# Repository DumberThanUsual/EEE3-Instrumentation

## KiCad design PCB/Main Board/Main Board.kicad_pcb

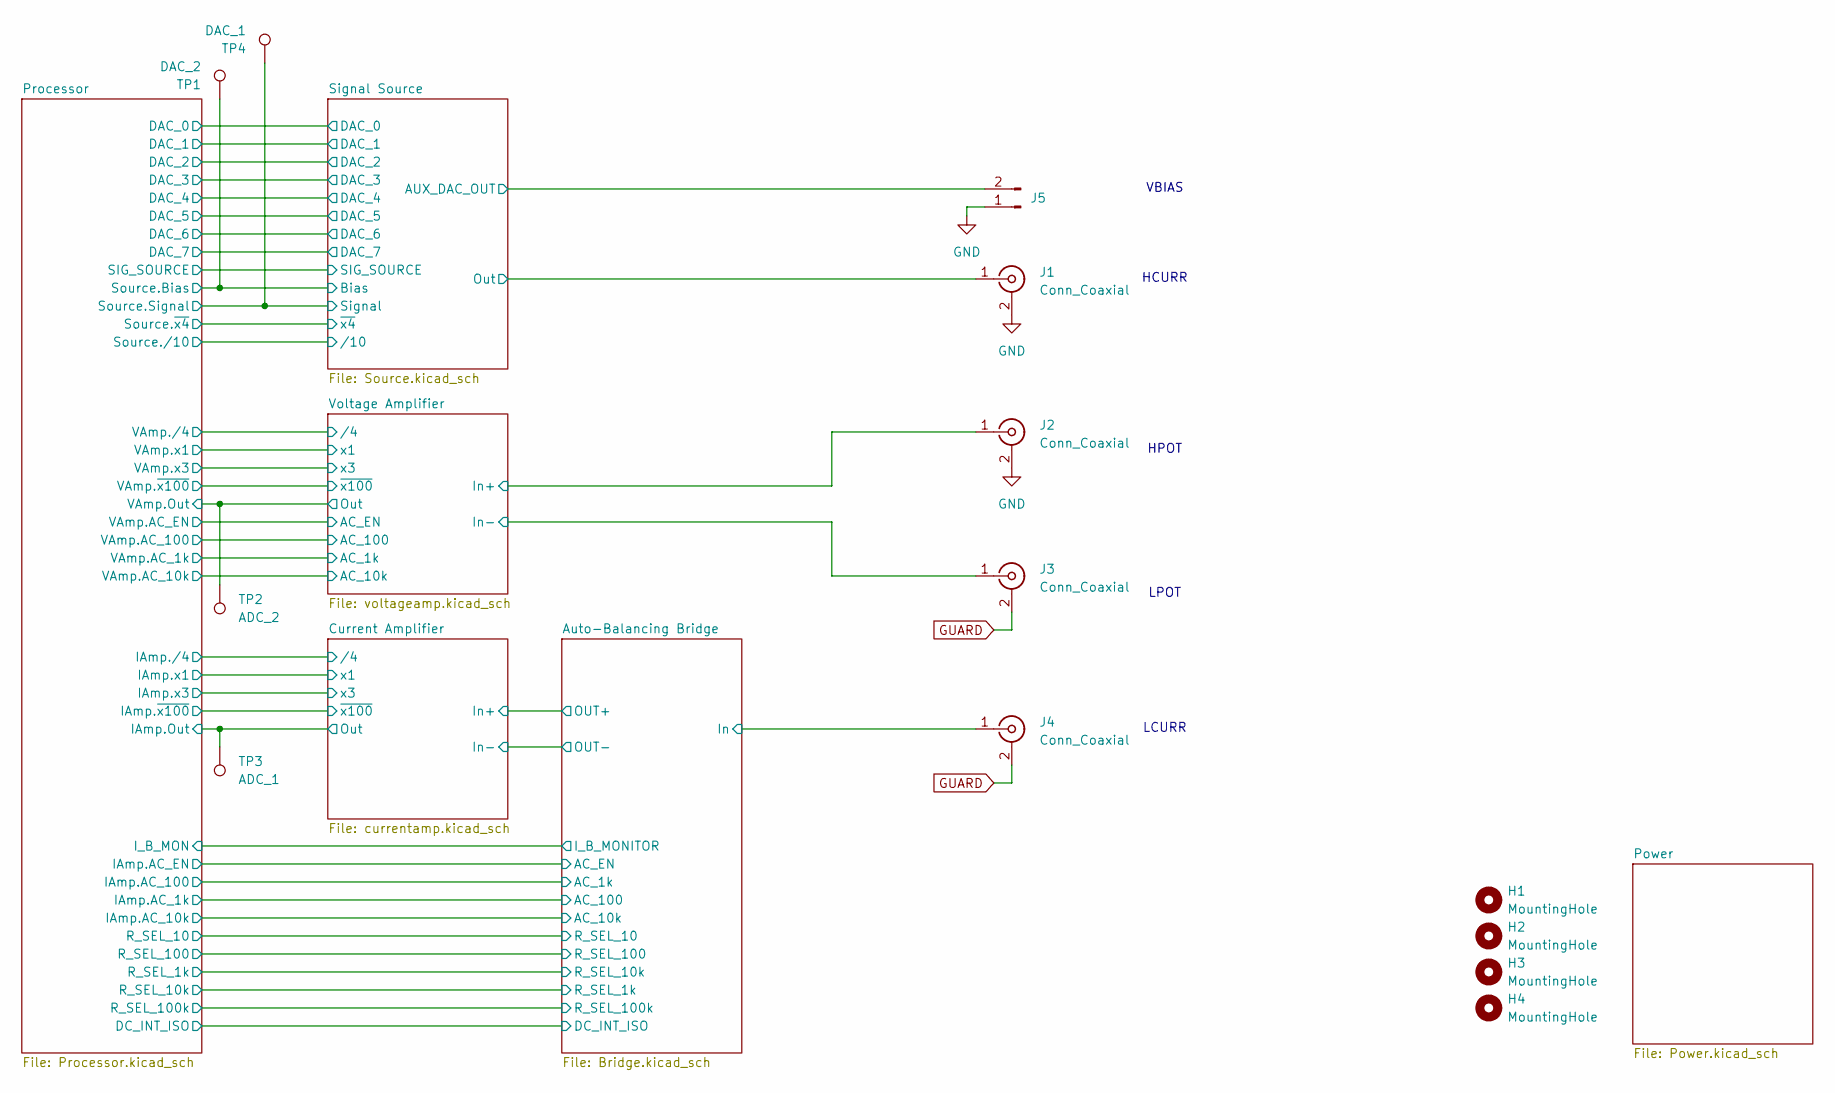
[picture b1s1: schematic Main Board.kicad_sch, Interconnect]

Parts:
H1, H2, H3, H4: MountingHole; MountingHole_3.2mm_M3
J1, J2, J3, J4: Conn_Coaxial; BNC_Amphenol_B6252HB-NPP3G-50_Horizontal
J5: Conn_01x02_Pin; PinHeader_1x02_P2.54mm_Vertical
TP1: DAC_2; TestPoint_Pad_2.0x2.0mm
TP2: ADC_2; TestPoint_Pad_2.0x2.0mm
TP3: ADC_1; TestPoint_Pad_2.0x2.0mm
TP4: DAC_1; TestPoint_Pad_2.0x2.0mm

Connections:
/Auto-Balancing Bridge/In: J4.1 (In); also elsewhere on the board
/Current Amplifier/Out: TP3.1; also elsewhere on the board
/Processor/Source.Bias: TP1.1; also elsewhere on the board
/Processor/Source.Signal: TP4.1; also elsewhere on the board
/Processor/VAmp.Out: TP2.1; also elsewhere on the board
/Signal Source/AUX_DAC_OUT: J5.2; also elsewhere on the board
/Signal Source/Out: J1.1 (In); also elsewhere on the board
/Voltage Amplifier/In+: J2.1 (In); also elsewhere on the board
/Voltage Amplifier/In-: J3.1 (In); also elsewhere on the board
GND: J1.2 (Ext), J2.2 (Ext), J5.1; also elsewhere on the board
GUARD: J3.2 (Ext), J4.2 (Ext); also elsewhere on the board

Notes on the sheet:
LPOT
HCURR
VBIAS
LCURR
HPOT

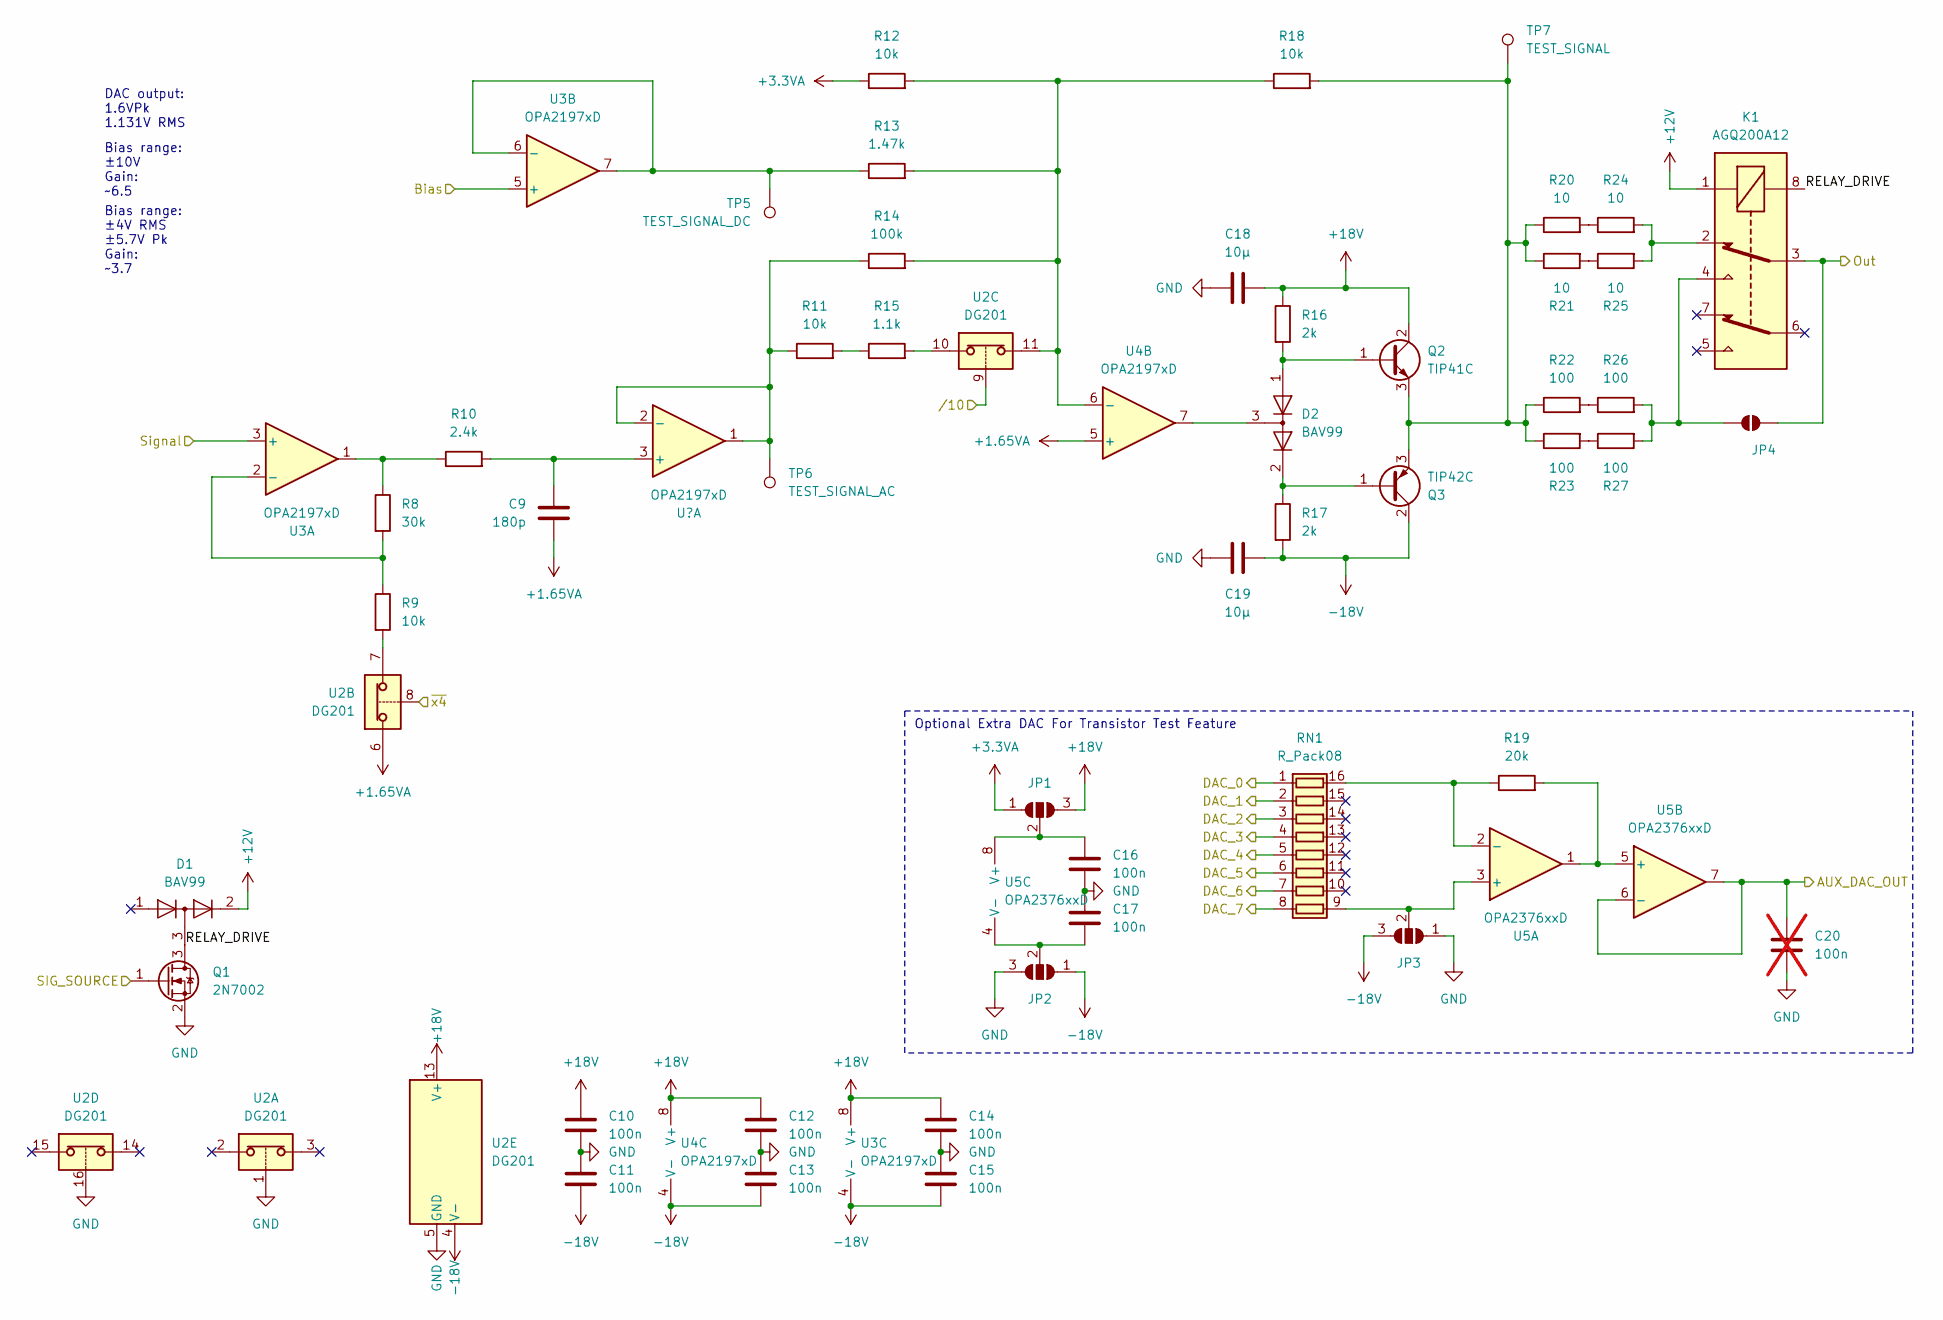
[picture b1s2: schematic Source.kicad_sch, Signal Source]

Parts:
C9: 180p; C_0805_2012Metric
C10, C11, C12, C13, C14, C15, C16, C17: 100n; C_0805_2012Metric
C18, C19: 10µ; C_0805_2012Metric
C20: 100n; C_0805_2012Metric; not fitted
D1, D2: BAV99; SOT-23
JP1, JP2, JP3: SolderJumper_3_Open; SolderJumper-3_P1.3mm_Open_RoundedPad1.0x1.5mm
JP4: SolderJumper_2_Open; SolderJumper-2_P1.3mm_Open_RoundedPad1.0x1.5mm
K1: AGQ200A12; RELAY_AGQ_A_PAN; Mouser Part Number 769-AGQ200A12
Q1: 2N7002; SOT-23
Q2: TIP41C; TO-220-3_Vertical
Q3: TIP42C; TO-220-3_Vertical
R8: 30k; R_0805_2012Metric
R9, R11, R12, R18: 10k; R_0805_2012Metric
R10: 2.4k; R_0805_2012Metric
R13: 1.47k; R_0805_2012Metric
R14: 100k; R_0805_2012Metric
R15: 1.1k; R_0805_2012Metric
R16, R17: 2k; R_0805_2012Metric
R19: 20k; R_0805_2012Metric
R20, R21, R24, R25: 10; R_2512_6332Metric
R22, R23, R26, R27: 100; R_0805_2012Metric
RN1: R_Pack08; SOIC-16_3.9x9.9mm_P1.27mm
TP5: TEST_SIGNAL_DC; TestPoint_Pad_2.0x2.0mm
TP6: TEST_SIGNAL_AC; TestPoint_Pad_2.0x2.0mm
TP7: TEST_SIGNAL; TestPoint_Pad_2.0x2.0mm
U2: DG201; SOIC-16_3.9x9.9mm_P1.27mm
U3, U4: OPA2197xD; SOIC-8_3.9x4.9mm_P1.27mm
U5: OPA2376xxD; SOIC-8_3.9x4.9mm_P1.27mm

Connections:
+1.65VA: C9.2, U2.6, U4.3 (+), U4.5 (+); also elsewhere on the board
+3.3VA: JP1.1 (A), R12.1; also elsewhere on the board
+12V: D1.2 (A), K1.1; also elsewhere on the board
+18V: C10.1, C12.1, C14.1, C18.2, JP1.3 (B), Q2.2 (C), R16.1, U2.13 (V+), U3.8 (V+), U4.8 (V+); also elsewhere on the board
-18V: C11.2, C13.2, C15.2, C19.2, JP2.1 (A), JP3.3 (B), Q3.2 (C), R17.2, U2.4 (V-), U3.4 (V-), U4.4 (V-); also elsewhere on the board
/Processor/DAC_0: RN1.1 (R1.1); also elsewhere on the board
/Processor/DAC_1: RN1.2 (R2.1); also elsewhere on the board
/Processor/DAC_2: RN1.3 (R3.1); also elsewhere on the board
/Processor/DAC_3: RN1.4 (R4.1); also elsewhere on the board
/Processor/DAC_4: RN1.5 (R5.1); also elsewhere on the board
/Processor/DAC_5: RN1.6 (R6.1); also elsewhere on the board
/Processor/DAC_6: RN1.7 (R7.1); also elsewhere on the board
/Processor/DAC_7: RN1.8 (R8.1); also elsewhere on the board
/Processor/SIG_SOURCE: Q1.1 (G); also elsewhere on the board
/Processor/Source.Bias: U3.5 (+); also elsewhere on the board
/Processor/Source.Signal: U3.3 (+); also elsewhere on the board
/Processor/Source./10: U2.9; also elsewhere on the board
/Processor/Source.~x4: U2.8; also elsewhere on the board
/Signal Source/AUX_DAC_OUT: C20.1, U5.6 (-), U5.7; also elsewhere on the board
/Signal Source/Out: JP4.1 (A), K1.3; also elsewhere on the board
/Signal Source/RELAY_DRIVE: D1.3 (K), K1.8, Q1.3 (D)
GND: C10.2, C11.1, C12.2, C13.1, C14.2, C15.1, C16.2, C17.1, C18.1, C19.1, C20.2, JP2.3 (B), JP3.1 (A), Q1.2 (S), U2.1, U2.5 (GND), U2.16; also elsewhere on the board
unnamed: D2.2 (A), Q3.1 (B), R17.1
unnamed: D2.3 (K), U4.7
unnamed: C16.1, JP1.2 (C), U5.8 (V+)
unnamed: C17.2, JP2.2 (C), U5.4 (V-)
unnamed: JP3.2 (C), RN1.9 (R8.2), U5.3 (+)
unnamed: JP4.2 (B), K1.4, R26.2, R27.2
unnamed: K1.2, R24.2, R25.2
unnamed: D2.1 (K), Q2.1 (B), R16.2
unnamed: Q2.3 (E), Q3.3 (E), R18.2, R20.1, R21.1, R22.1, R23.1, TP7.1
unnamed: R9.2, U2.7
unnamed: R8.1, R10.1, U3.1
unnamed: R11.1, R14.1, TP6.1, U4.1
unnamed: R11.2, R15.1
unnamed: R15.2, U2.10
unnamed: R20.2, R24.1
unnamed: R21.2, R25.1
unnamed: R22.2, R26.1
unnamed: R23.2, R27.1
unnamed: R19.1, RN1.16 (R1.2), U5.2 (-)
unnamed: R8.2, R9.1, U3.2 (-)
unnamed: R13.1, TP5.1, U3.6 (-), U3.7
unnamed: C9.1, R10.2, U4.2 (-)
unnamed: R12.2, R13.2, R14.2, R18.1, U2.11, U4.6 (-)
unnamed: R19.2, U5.1, U5.5 (+)

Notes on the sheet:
Optional Extra DAC For Transistor Test Feature
Bias range: ±10V Gain: ~6.5
DAC output: 1.6VPk 1.131V RMS
Bias range: ±4V RMS ±5.7V Pk Gain: ~3.7

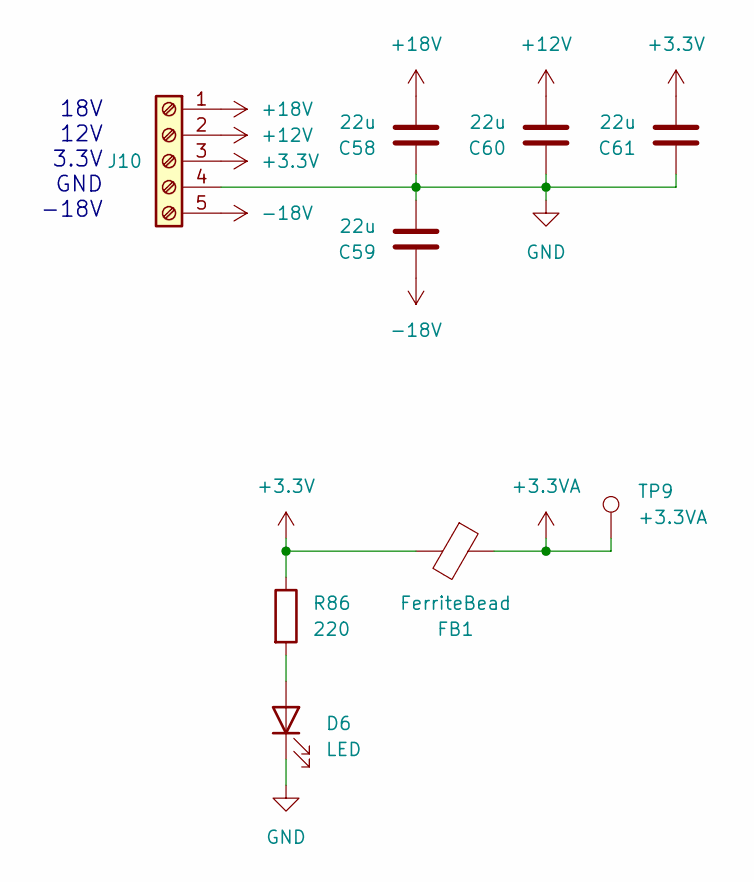
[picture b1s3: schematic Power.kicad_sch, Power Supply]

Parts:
C58, C59, C60, C61: 22u; C_1210_3225Metric
D6: LED; LED_0805_2012Metric
FB1: FerriteBead; L_0805_2012Metric
J10: Screw_Terminal_01x05; TerminalBlock_Phoenix_MKDS-1,5-5_1x05_P5.00mm_Horizontal
R86: 220; R_0805_2012Metric
TP9: +3.3VA; TestPoint_Pad_2.0x2.0mm

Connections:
+3.3V: C61.2, FB1.2, J10.3, R86.1; also elsewhere on the board
+3.3VA: FB1.1, TP9.1; also elsewhere on the board
+12V: C60.2, J10.2; also elsewhere on the board
+18V: C58.2, J10.1; also elsewhere on the board
-18V: C59.1, J10.5; also elsewhere on the board
GND: C58.1, C59.2, C60.1, C61.1, D6.1 (K), J10.4; also elsewhere on the board
unnamed: D6.2 (A), R86.2

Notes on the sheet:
18V 12V 3.3V GND -18V

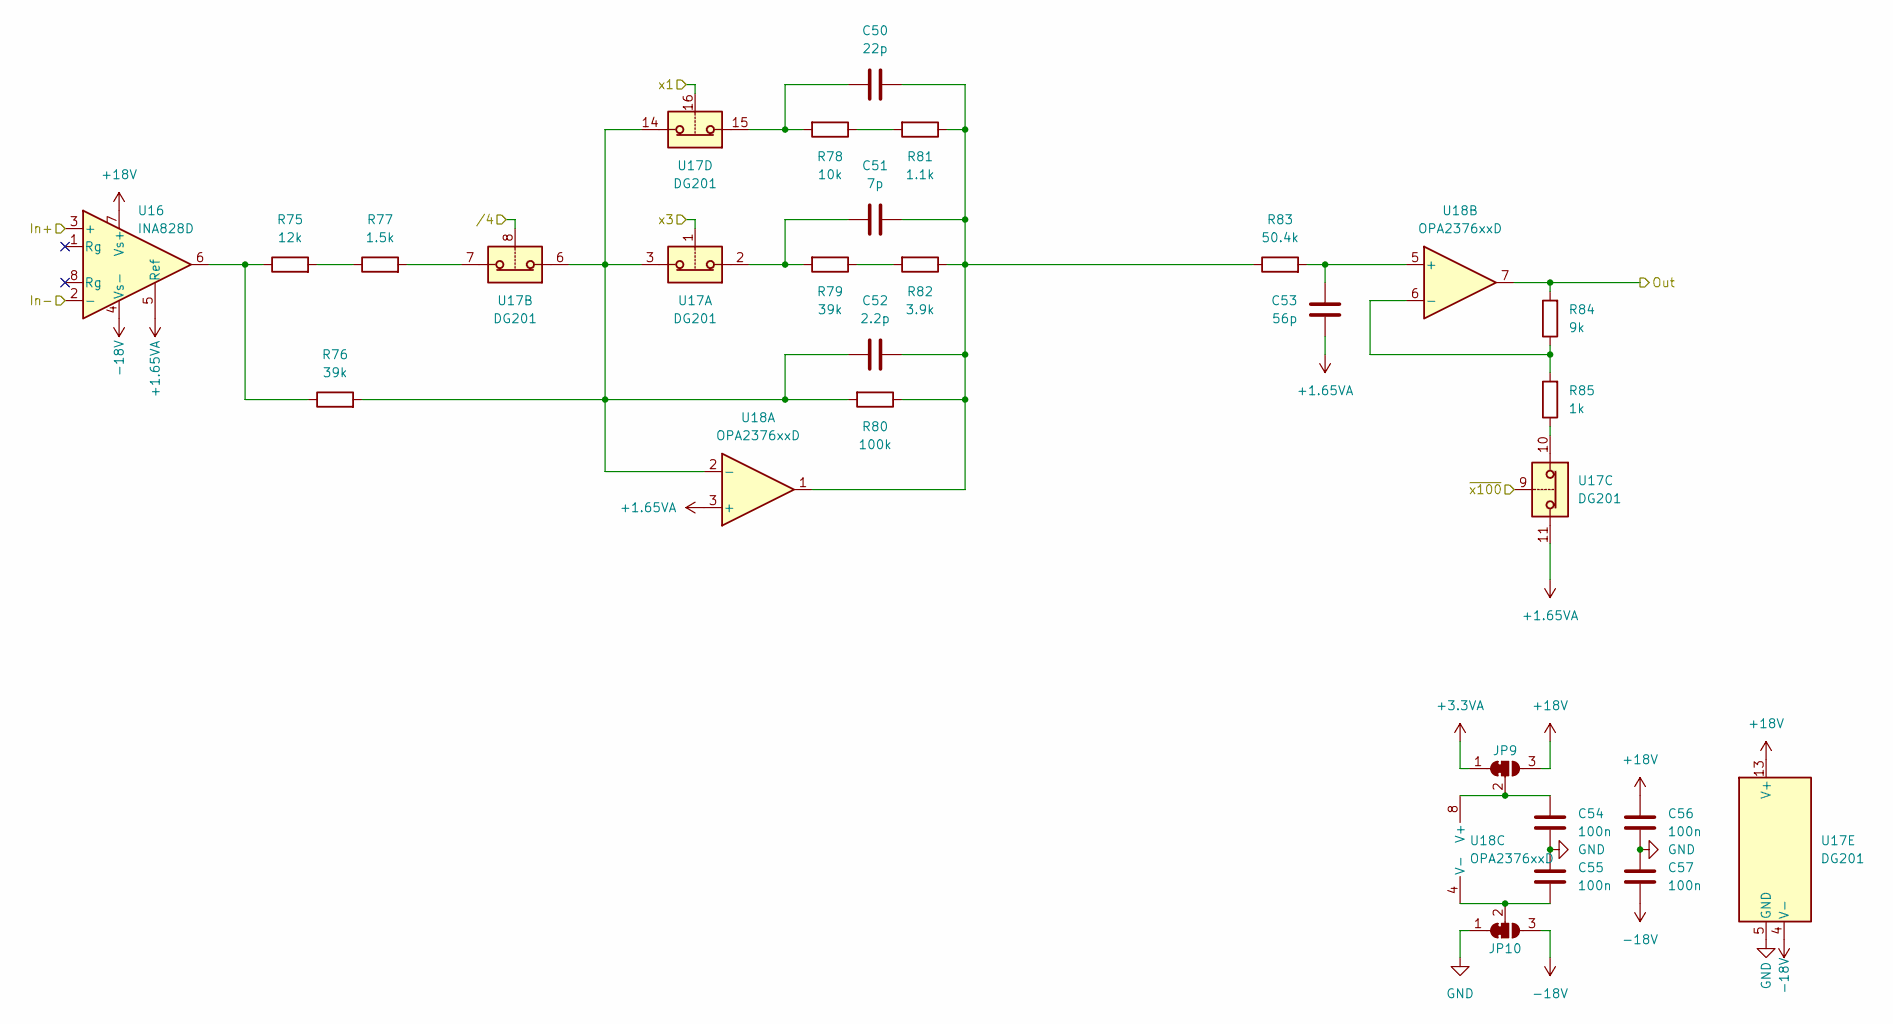
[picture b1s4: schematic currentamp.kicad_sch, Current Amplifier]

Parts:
C50: 22p; C_0805_2012Metric
C51: 7p; C_0805_2012Metric
C52: 2.2p; C_0805_2012Metric
C53: 56p; C_0805_2012Metric
C54, C55, C56, C57: 100n; C_0805_2012Metric
JP9, JP10: SolderJumper_3_Bridged12; SolderJumper-3_P1.3mm_Bridged12_RoundedPad1.0x1.5mm
R75: 12k; R_0805_2012Metric
R76, R79: 39k; R_0805_2012Metric
R77: 1.5k; R_0805_2012Metric
R78: 10k; R_0805_2012Metric
R80: 100k; R_0805_2012Metric
R81: 1.1k; R_0805_2012Metric
R82: 3.9k; R_0805_2012Metric
R83: 50.4k; R_0805_2012Metric
R84: 9k; R_0805_2012Metric
R85: 1k; R_0805_2012Metric
U16: INA828D; SOIC-8_3.9x4.9mm_P1.27mm
U17: DG201; SOIC-16_3.9x9.9mm_P1.27mm
U18: OPA2376xxD; SOIC-8_3.9x4.9mm_P1.27mm

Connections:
+1.65VA: C53.2, U16.5 (Ref), U17.11, U18.3 (+); also elsewhere on the board
+3.3VA: JP9.1 (A); also elsewhere on the board
+18V: C56.1, JP9.3 (B), U16.7 (Vs+), U17.13 (V+); also elsewhere on the board
-18V: C57.2, JP10.3 (B), U16.4 (Vs-), U17.4 (V-); also elsewhere on the board
/Auto-Balancing Bridge/In: U16.3 (+); also elsewhere on the board
/Auto-Balancing Bridge/OUT+: U16.2 (-); also elsewhere on the board
/Current Amplifier/Out: R84.2, U18.7; also elsewhere on the board
/Current Amplifier/x1: U17.16; also elsewhere on the board
/Current Amplifier/x3: U17.1; also elsewhere on the board
/Current Amplifier//4: U17.8; also elsewhere on the board
/Current Amplifier/~x100: U17.9; also elsewhere on the board
GND: C54.2, C55.1, C56.2, C57.1, JP10.1 (A), U17.5 (GND); also elsewhere on the board
unnamed: C50.1, R78.2, U17.15
unnamed: C50.2, C51.2, C52.2, R80.1, R81.1, R82.1, R83.1, U18.1
unnamed: C51.1, R79.2, U17.2
unnamed: C54.1, JP9.2 (C), U18.8 (V+)
unnamed: C55.2, JP10.2 (C), U18.4 (V-)
unnamed: R75.1, R76.1, U16.6
unnamed: R75.2, R77.1
unnamed: R77.2, U17.7
unnamed: R78.1, R81.2
unnamed: R79.1, R82.2
unnamed: R85.1, U17.10
unnamed: C52.1, R76.2, R80.2, U17.3, U17.6, U17.14, U18.2 (-)
unnamed: C53.1, R83.2, U18.5 (+)
unnamed: R84.1, R85.2, U18.6 (-)

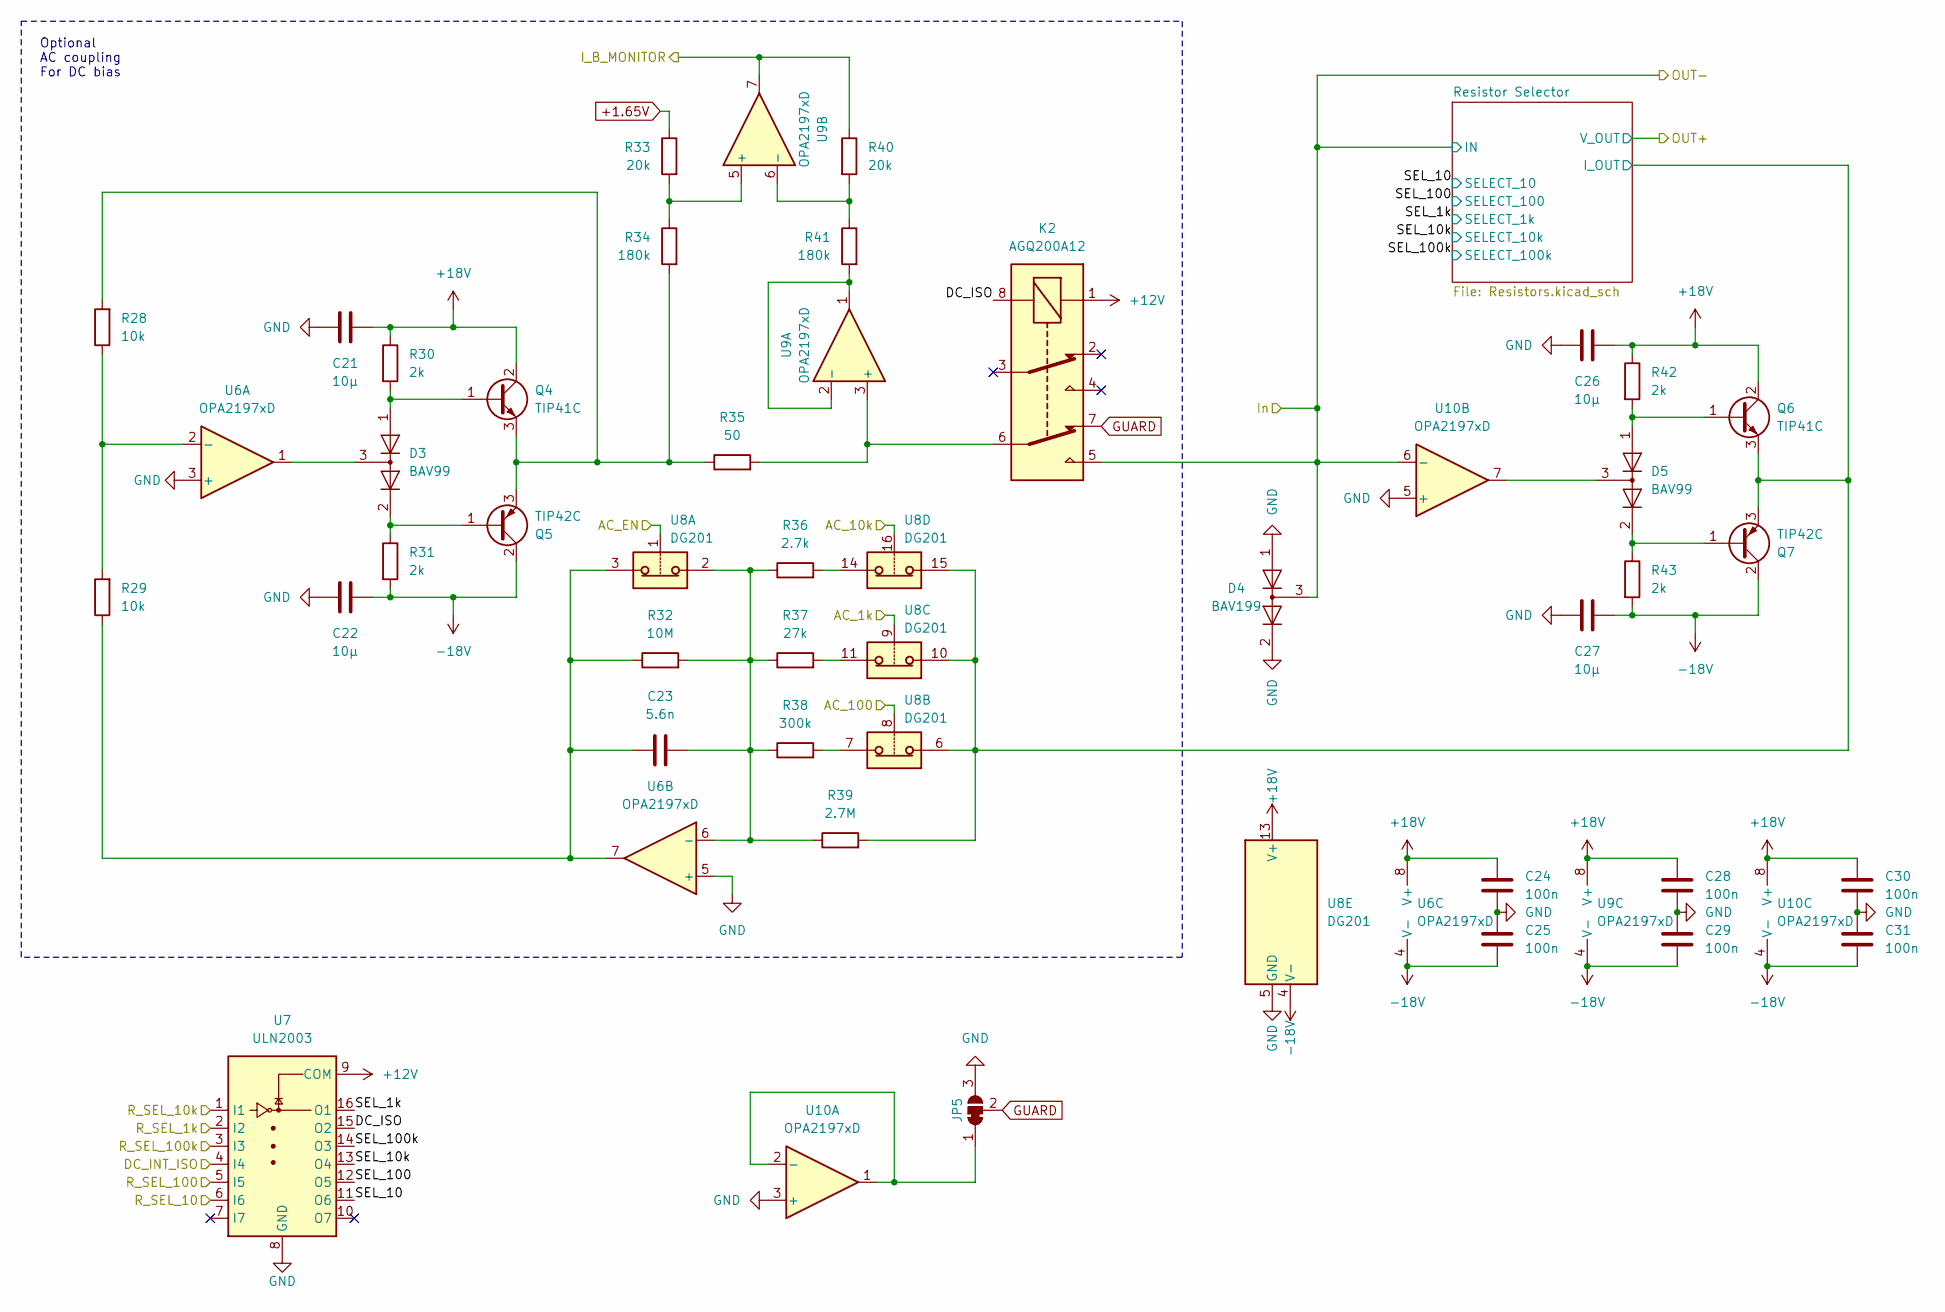
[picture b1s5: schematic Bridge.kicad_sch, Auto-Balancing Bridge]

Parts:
C21, C22, C26, C27: 10µ; C_0805_2012Metric
C23: 5.6n; C_0805_2012Metric
C24, C25, C28, C29, C30, C31: 100n; C_0805_2012Metric
D3, D5: BAV99; SOT-23
D4: BAV199; SOT-23
JP5: SolderJumper_3_Bridged12; SolderJumper-3_P1.3mm_Bridged12_RoundedPad1.0x1.5mm
K2: AGQ200A12; RELAY_AGQ_A_PAN; Mouser Part Number 769-AGQ200A12
Q4, Q6: TIP41C; TO-220-3_Vertical
Q5, Q7: TIP42C; TO-220-3_Vertical
R28, R29: 10k; R_0805_2012Metric
R30, R31, R42, R43: 2k; R_0805_2012Metric
R32: 10M; R_0805_2012Metric
R33, R40: 20k; R_0805_2012Metric
R34, R41: 180k; R_0805_2012Metric
R35: 50; R_0805_2012Metric
R36: 2.7k; R_0805_2012Metric
R37: 27k; R_0805_2012Metric
R38: 300k; R_0805_2012Metric
R39: 2.7M; R_0805_2012Metric
U6, U9, U10: OPA2197xD; SOIC-8_3.9x4.9mm_P1.27mm
U7: ULN2003; SOIC-16_3.9x9.9mm_P1.27mm
U8: DG201; SOIC-16_3.9x9.9mm_P1.27mm

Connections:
+1.65V: R33.1
+12V: K2.1, U7.9 (COM); also elsewhere on the board
+18V: C21.2, C24.1, C26.2, C28.1, C30.1, Q4.2 (C), Q6.2 (C), R30.1, R42.1, U6.8 (V+), U8.13 (V+), U9.8 (V+), U10.8 (V+); also elsewhere on the board
-18V: C22.2, C25.2, C27.2, C29.2, C31.2, Q5.2 (C), Q7.2 (C), R31.2, R43.2, U6.4 (V-), U8.4 (V-), U9.4 (V-), U10.4 (V-); also elsewhere on the board
/Auto-Balancing Bridge/AC_1k: U8.9; also elsewhere on the board
/Auto-Balancing Bridge/AC_10k: U8.16; also elsewhere on the board
/Auto-Balancing Bridge/AC_100: U8.8; also elsewhere on the board
/Auto-Balancing Bridge/AC_EN: U8.1; also elsewhere on the board
/Auto-Balancing Bridge/DC_INT_ISO: U7.4 (I4); also elsewhere on the board
/Auto-Balancing Bridge/DC_ISO: K2.8, U7.15 (O2)
/Auto-Balancing Bridge/I_B_MONITOR: R40.1, U9.7; also elsewhere on the board
/Auto-Balancing Bridge/In: D4.3 (K), K2.5, U10.6 (-); also elsewhere on the board
/Auto-Balancing Bridge/OUT+: Q6.3 (E), Q7.3 (E), R39.2, U8.6, U8.10, U8.15; also elsewhere on the board
/Auto-Balancing Bridge/R_SEL_1k: U7.2 (I2); also elsewhere on the board
/Auto-Balancing Bridge/R_SEL_10: U7.6 (I6); also elsewhere on the board
/Auto-Balancing Bridge/R_SEL_10k: U7.1 (I1); also elsewhere on the board
/Auto-Balancing Bridge/R_SEL_100: U7.5 (I5); also elsewhere on the board
/Auto-Balancing Bridge/R_SEL_100k: U7.3 (I3); also elsewhere on the board
/Auto-Balancing Bridge/SEL_1k: U7.16 (O1); also elsewhere on the board
/Auto-Balancing Bridge/SEL_10: U7.11 (O6); also elsewhere on the board
/Auto-Balancing Bridge/SEL_10k: U7.13 (O4); also elsewhere on the board
/Auto-Balancing Bridge/SEL_100: U7.12 (O5); also elsewhere on the board
/Auto-Balancing Bridge/SEL_100k: U7.14 (O3); also elsewhere on the board
GND: C21.1, C22.1, C24.2, C25.1, C26.1, C27.1, C28.2, C29.1, C30.2, C31.1, D4.1 (K), D4.2 (A), JP5.3 (B), U6.3 (+), U6.5 (+), U7.8 (GND), U8.5 (GND), U10.3 (+), U10.5 (+); also elsewhere on the board
GUARD: JP5.2 (C), K2.7; also elsewhere on the board
unnamed: C23.1, R29.1, R32.1, U6.7, U8.3
unnamed: D3.2 (A), Q5.1 (B), R31.1
unnamed: D3.3 (K), U6.1
unnamed: D5.2 (A), Q7.1 (B), R43.1
unnamed: D5.3 (K), U10.7
unnamed: JP5.1 (A), U10.1, U10.2 (-)
unnamed: D3.1 (K), Q4.1 (B), R30.2
unnamed: Q4.3 (E), Q5.3 (E), R28.2, R34.2, R35.1
unnamed: D5.1 (K), Q6.1 (B), R42.2
unnamed: R36.2, U8.14
unnamed: R37.2, U8.11
unnamed: R38.2, U8.7
unnamed: R28.1, R29.2, U6.2 (-)
unnamed: C23.2, R32.2, R36.1, R37.1, R38.1, R39.1, U6.6 (-), U8.2
unnamed: K2.6, R35.2, U9.3 (+)
unnamed: R41.2, U9.1, U9.2 (-)
unnamed: R33.2, R34.1, U9.5 (+)
unnamed: R40.2, R41.1, U9.6 (-)

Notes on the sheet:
Optional AC coupling For DC bias

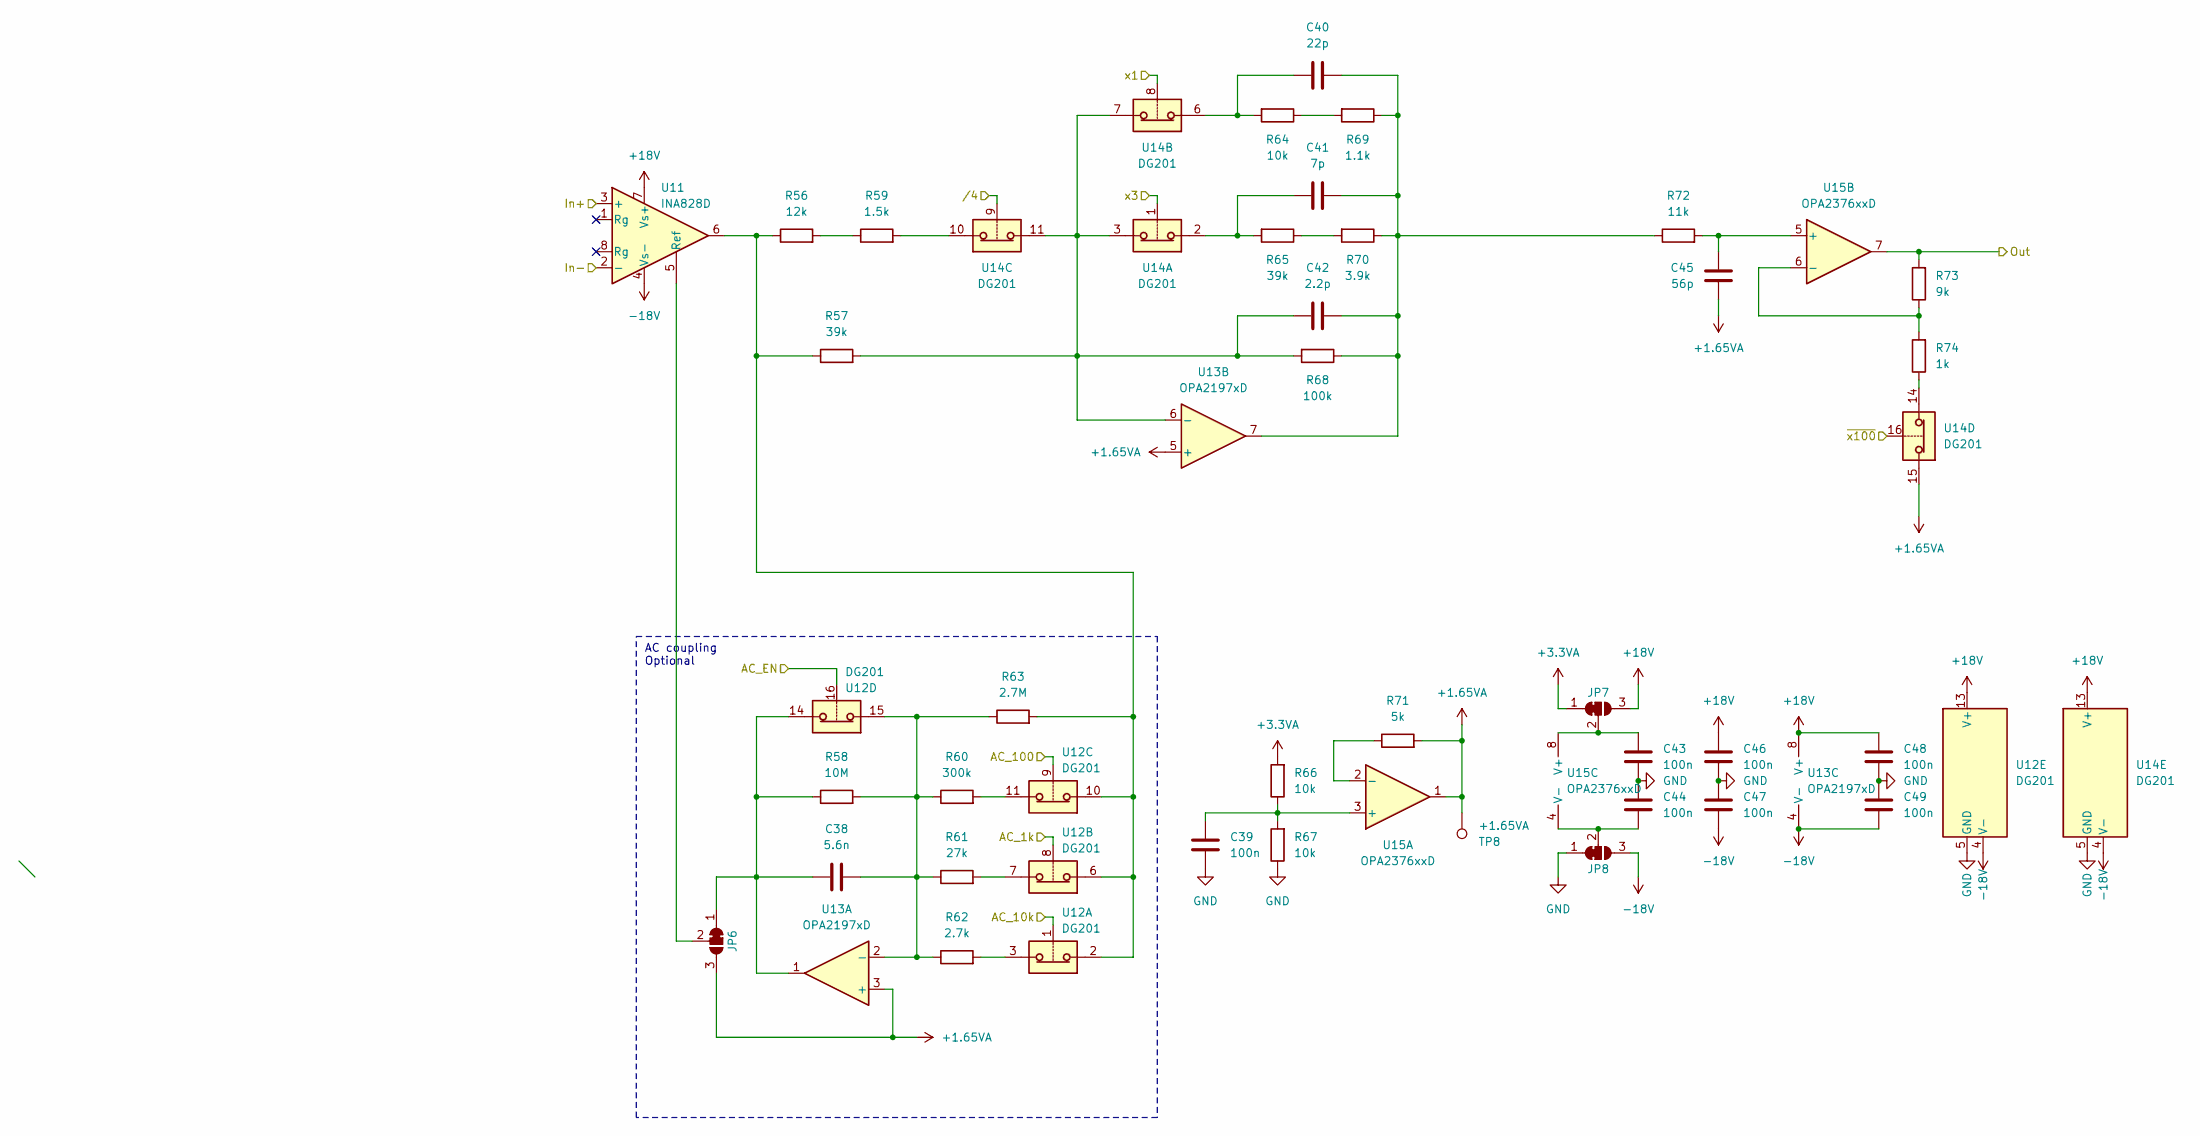
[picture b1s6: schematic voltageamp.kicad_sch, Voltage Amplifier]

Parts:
C38: 5.6n; C_0805_2012Metric
C39, C43, C44, C46, C47, C48, C49: 100n; C_0805_2012Metric
C40: 22p; C_0805_2012Metric
C41: 7p; C_0805_2012Metric
C42: 2.2p; C_0805_2012Metric
C45: 56p; C_0805_2012Metric
JP6, JP7, JP8: SolderJumper_3_Bridged12; SolderJumper-3_P1.3mm_Bridged12_RoundedPad1.0x1.5mm_NumberL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
R56: 12k; R_0805_2012Metric
R57, R65: 39k; R_0805_2012Metric
R58: 10M; R_0805_2012Metric
R59: 1.5k; R_0805_2012Metric
R60: 300k; R_0805_2012Metric
R61: 27k; R_0805_2012Metric
R62: 2.7k; R_0805_2012Metric
R63: 2.7M; R_0805_2012Metric
R64, R66, R67: 10k; R_0805_2012Metric
R68: 100k; R_0805_2012Metric
R69: 1.1k; R_0805_2012Metric
R70: 3.9k; R_0805_2012Metric
R71: 5k; R_0805_2012Metric
R72: 11k; R_0805_2012Metric
R73: 9k; R_0805_2012Metric
R74: 1k; R_0805_2012Metric
TP8: +1.65VA; TestPoint_Pad_2.0x2.0mm
U11: INA828D; SOIC-8_3.9x4.9mm_P1.27mm
U12, U14: DG201; SOIC-16_3.9x9.9mm_P1.27mm
U13: OPA2197xD; SOIC-8_3.9x4.9mm_P1.27mm
U15: OPA2376xxD; SOIC-8_3.9x4.9mm_P1.27mm

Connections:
+1.65VA: C45.2, JP6.3 (B), R71.2, TP8.1, U13.3 (+), U13.5 (+), U14.15, U15.1; also elsewhere on the board
+3.3VA: JP7.1 (A), R66.2; also elsewhere on the board
+18V: C46.1, C48.1, JP7.3 (B), U11.7 (Vs+), U12.13 (V+), U13.8 (V+), U14.13 (V+); also elsewhere on the board
-18V: C47.2, C49.2, JP8.3 (B), U11.4 (Vs-), U12.4 (V-), U13.4 (V-), U14.4 (V-); also elsewhere on the board
/Processor/VAmp.AC_1k: U12.8; also elsewhere on the board
/Processor/VAmp.AC_10k: U12.1; also elsewhere on the board
/Processor/VAmp.AC_100: U12.9; also elsewhere on the board
/Processor/VAmp.AC_EN: U12.16; also elsewhere on the board
/Processor/VAmp.Out: R73.2, U15.7; also elsewhere on the board
/Processor/VAmp.x1: U14.8; also elsewhere on the board
/Processor/VAmp.x3: U14.1; also elsewhere on the board
/Processor/VAmp./4: U14.9; also elsewhere on the board
/Processor/VAmp.~x100: U14.16; also elsewhere on the board
/Voltage Amplifier/In+: U11.3 (+); also elsewhere on the board
/Voltage Amplifier/In-: U11.2 (-); also elsewhere on the board
GND: C39.2, C43.2, C44.1, C46.2, C47.1, C48.2, C49.1, JP8.1 (A), R67.1, U12.5 (GND), U14.5 (GND); also elsewhere on the board
unnamed: C40.1, R64.2, U14.6
unnamed: C40.2, C41.2, C42.2, R68.1, R69.1, R70.1, R72.1, U13.7
unnamed: C41.1, R65.2, U14.2
unnamed: C38.1, JP6.1 (A), R58.1, U12.14, U13.1
unnamed: JP6.2 (C), U11.5 (Ref)
unnamed: C43.1, JP7.2 (C), U15.8 (V+)
unnamed: C44.2, JP8.2 (C), U15.4 (V-)
unnamed: R56.1, R57.1, R63.2, U11.6, U12.2, U12.6, U12.10
unnamed: R56.2, R59.1
unnamed: R59.2, U14.10
unnamed: R60.2, U12.11
unnamed: R61.2, U12.7
unnamed: R62.2, U12.3
unnamed: R64.1, R69.2
unnamed: R65.1, R70.2
unnamed: R74.1, U14.14
unnamed: C38.2, R58.2, R60.1, R61.1, R62.1, R63.1, U12.15, U13.2 (-)
unnamed: C42.1, R57.2, R68.2, U13.6 (-), U14.3, U14.7, U14.11
unnamed: C39.1, R66.1, R67.2, U15.3 (+)
unnamed: R71.1, U15.2 (-)
unnamed: C45.1, R72.2, U15.5 (+)
unnamed: R73.1, R74.2, U15.6 (-)

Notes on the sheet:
AC coupling Optional
